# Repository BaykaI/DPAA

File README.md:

# DPAA — ЦАФАР, которую можно услышать

Проект демонстрации принципов **цифровой активной фазированной антенной решётки
(ЦАФАР)** в акустическом диапазоне: вместо антенн — динамики и микрофоны, вместо
СВЧ — звук 1.5–4 кГц, вместо осциллографа — уши зрителей.

Звук в ~875 000 раз медленнее радиоволн, поэтому решётка из восьми динамиков
с шагом 4 см геометрически эквивалентна решётке S-диапазона, а обычная
многоканальная звуковая карта оцифровывает сигнал прямо на «несущей» — то, о чём
мечтают разработчики настоящих ЦАФАР.

Подробная концепция, расчёты, сценарии и варианты железа: **[docs/concept.md](docs/concept.md)**.

**Железо** (16 элементов, ПЛИС ECP5 на модуле Colorlight i9, ≈ 630 $, с резервом ≈ 725 $ из 1000 $):
[архитектура](docs/hardware/architecture.md) · [что купить и заказать](docs/hardware/purchase.md) · [спецификация и бюджет](docs/hardware/bom.md) ·
[схемы плат](docs/hardware/schematics.md) · [распиновка](docs/hardware/pinout.md) ·
[схема соединений](docs/hardware/wiring.md) · [полная структурная схема](docs/img/full_diagram.svg) · [элемент: динамик + микрофон, 3D-модель](docs/hardware/mechanics.md) ·
[прошивка ПЛИС](gateware/README.md)

## Что уже есть

* `dpaa/` — небольшая библиотека моделирования:
  * `geometry.py` — решётки (линейные, плоские), направления, задержки фазирования;
  * `signals.py` — дробные задержки (БПФ и КИХ для реального времени), фазовращатель,
    тестовые сигналы;
  * `patterns.py` — диаграммы направленности, весовые окна, «косоглазие» луча, квантование;
  * `propagation.py` — распространение звука в свободном поле;
  * `transmit.py` — формирование лучей на передачу, многолучевость, сканирование, запись WAV;
  * `beamforming.py` — приём: задержка-сумма, MVDR (Кейпон), «акустическая камера».
* `scripts/`:
  * `design_calc.py` — таблицы параметров решётки;
  * `plot_patterns.py` — иллюстрации в `docs/img/`;
  * `make_tx_demo.py` — 8-канальные WAV для реальной решётки динамиков и
    **моно-WAV «виртуальных слушателей»** — можно послушать эффект в наушниках уже сейчас;
  * `demo_rx_sim.py` — приём двумя лучами и адаптивное подавление помехи.
* `dpaa/hw.py` — аппаратная модель: карта регистров, протокол UART, фиксированная точка,
  эталонная модель ядра ПЛИС (RTL сверяется с ней бит в бит).
* `gateware/` — прошивка ПЛИС на Verilog: I2S на 16 усилителей и 17 микрофонов,
  генераторы, цифровое диаграммообразование на передачу (2 луча) и приём (2 луча).
* `tools/dpaa_ctl.py` — управление с ноутбука: луч, сканирование, два луча, фокус,
  поэлементный тест, лучи приёма в наушники, уровни микрофонов.
* `software/DpaaControl/` — **пульт управления на C#** (.NET 8 + Avalonia, Windows/Linux/macOS):
  все сценарии `dpaa_ctl.py` с ползунками, план зала с лепестком звука, диаграмма
  направленности, уровни микрофонов, симулятор ПЛИС для работы без железа —
  [README](software/DpaaControl/README.md).
* `firmware/esp32/` — **прошивка Wi-Fi-пульта ESP32-S3**: своя сеть Wi-Fi, страница для планшета
  (луч «пальцем», маятник, два луча, прожектор, приём), автопилот для музея, служебная панель —
  [README](firmware/esp32/README.md).
* `tests/` — проверки физики и алгоритмов и RTL-тесты ПЛИС (`pytest`, нужен Icarus Verilog).

## Быстрый старт

```bash
pip install -r requirements.txt
python -m pytest -q                 # тесты
python scripts/design_calc.py       # расчёт параметров
python scripts/plot_patterns.py     # графики -> docs/img/
python scripts/make_tx_demo.py      # WAV -> out/tx/
python scripts/demo_rx_sim.py       # WAV -> out/rx/
```

Послушать без железа: `out/tx/listen_two_beams_-35deg.wav` и `..._+35deg.wav` —
что слышат два человека, стоящие по разные стороны от решётки, воспроизводящей
два луча одновременно; `out/tx/listen_prism_phase_*` — «звуковая призма»;
`out/rx/mic1.wav` vs `out/rx/mvdr_target.wav` — подавление помехи на приёме.

## Соглашения

Решётка лежит вдоль оси x и излучает вдоль +y. Угол отсчитывается от нормали,
положительные углы — вправо, если стоять за решёткой и смотреть в направлении
излучения. Канал 1 многоканального WAV — крайний левый элемент.

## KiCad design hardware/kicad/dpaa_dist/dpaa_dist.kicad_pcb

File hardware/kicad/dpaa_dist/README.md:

# Распределительная плата DPAA (A3) — проект KiCad 10

Плата 100 × 180 мм, два слоя, все компоненты на верхней стороне, сборка на фабрике (JLCPCB/PCBWay).
13 буферов 74LVC244 (SOIC-20W; U1–U8 — такты пары соседних элементов, U9–U12 — TXD/MIC четырёх
элементов, U13 — ЦАП и зонд), ЦАП PCM5102A, драйвер наушников TDA1308, два стабилизатора
AP2112K-3.3, защита питания (P-MOSFET AO4407A, TVS SMBJ5.0A, 1000 мкФ), 4 предохранителя PTC,
16 гребёнок элементов 2×6, три вилки IDC 2×15 к плате ПЛИС (P1 — Ethernet, P2, P3 — сигналы), RJ45 зонда,
гнездо Ethernet RJ45 с трансформаторами (MagJack), ESP32, наушники.
Схема — [`../../../docs/hardware/schematics.md`](../../../docs/hardware/schematics.md).

## Файлы

| Файл | Что |
|---|---|
| `dpaa_dist.kicad_pro`, `.kicad_sch`, `.kicad_pcb` | проект, схема, плата (открываются в KiCad 10) |
| `fab/dpaa_dist_gerber.zip` | Gerber (RS-274X) + Excellon + карта сверловки |
| `fab/dpaa_dist_bom_jlcpcb.csv`, `fab/dpaa_dist_cpl_jlcpcb.csv` | BOM и координаты SMD в формате JLCPCB |
| `fab/dpaa_dist_bom.csv`, `fab/dpaa_dist_pos.csv` | BOM (с наименованиями для заказа) и координаты всех компонентов |
| `fab/dpaa_dist_top.pdf`, `_bottom.pdf`, `_assembly.pdf`, `_schematic.pdf` | слои, сборочный чертёж, схема |
| `fab/render_top.png`, `render_bottom.png`, `render_3d.png`, `dpaa_dist.step` | 3D-вид и модель |
| `drc.json`, `erc.json` | отчёты DRC/ERC (сводка — `python gen/drc_report.py`) |

## Как собрано

Схема и плата **генерируются скриптами** (`gen/`), вручную в KiCad ничего не рисовалось:

* `gen/place.py` — компоновка и цепи (все корпуса — в узлах сетки 0,635 мм);
* `gen/router.py` — трассировщик по сетке (A*, два слоя: верхний — горизонтали, нижний — вертикали,
  перекладка мешающих цепей при неудаче);
* `gen/make_board.py` — сборка платы: силовые шины 1 мм вручную (+5 В по нижнему краю, 5 В групп
  и 3V3_MIC вдоль боковых краёв), остальные цепи — трассировщиком (0,25 мм, переходные 0,6/0,3),
  земля — дорожками и полигонами на обоих слоях, затем проход `miter_corners()`: каждый прямой
  угол заменяется двумя поворотами по 45° (прямых углов на дорожках нет);
* `gen/make_sch.py` — схема из платы: прямоугольные символы с номерами выводов посадочных мест,
  цепи — глобальными метками (ERC сверяет схему с платой по именам цепей);
* `gen/fix_pro.py` — нормы фабрики в проекте: зазор 0,2, дорожка 0,2, отверстие 0,3, медь до края 0,3.

Запуск: `gen/build.sh` (плата → DRC → схема → ERC → сводка), затем `gen/export.sh` (пакет для фабрики).
Нужны KiCad 10 (`kicad-cli`, его Python) и системный Python 3.

## Нумерация и назначение разъёмов

* **J1–J16** — элементы 1–16 (J1–J8 слева сверху вниз, J9–J16 справа), контакт 1 у края платы:
  нечётный ряд — к модулю усилителя MAX98357A, чётный — к микрофону ICS-43434 (таблица в
  [`pinout.md`](../../../docs/hardware/pinout.md)). 5 В на контакт 1 идёт через предохранитель
  своей группы: F1 — J1–J4, F2 — J5–J8, F3 — J9–J12, F4 — J13–J16.
* **J19** = гребёнка **P1** (Ethernet), **J20** = гребёнка **P2**, **J21** = гребёнка **P3** платы расширения
  Colorlight i9: три одинаковых прямых шлейфа IDC 2×15 (жила n → контакт n обоих разъёмов). Гребёнки платы
  расширения нумерованы «1–15 в одном ряду, 16–30 в другом (30 напротив 1)», а вилка IDC — зигзагом
  (1, 2 в первой колонке, 3, 4 во второй…); прямой шлейф соединяет контакты **по положению**, поэтому
  на плате сигнал контакта *d* гребёнки стоит на контакте вилки 2d−1 (d ≤ 15) или 2·(31−d) (d ≥ 16) —
  это учтено в генераторе (`dip2k()` в `gen/place.py`). Ключ вилки — в сторону контакта 1; на плате
  расширения ключа нет, контакт 1 шлейфа (цветная жила) — на контакт 1 гребёнки (у надписи P1/P2/P3).
  Контакты 3V3 и 5V гребёнок на плате не подключены.
* **J17** — RJ45 зонда (T568B: 1 BCLK, 3 LRCLK, 4–5 3V3_MIC, 7 SD, 2/6/8 GND).
* **J18** — питание 5 В 5.5/2.1 мм (центр «+»); **J25** — ESP32 (TX, RX, GND); **J26, J27** — наушники.
* **SW1** — кнопка «тестовый тон» (BTN_TEST → 3,3 В); LED1 — 5 В, LED2 — 3,3 В логики.

## Ethernet (J19 → J29)

Что это. На модуле Colorlight i9 стоят два гигабитных PHY Broadcom B50612D; их линейные пары MDI
(после PHY, без трансформаторов) выведены на гребёнку **P1** платы расширения. На распределительной
плате порт ETH1 заведён на гнездо **J29** — RJ45 MagJack **UDE RB1-125B8G1A** (LCSC C363353,
1000BASE-T, трансформаторы, терминация Боба Смита 75 Ом × 4 + 1000 пФ 2 кВ внутри — её общий вывод R10
и экран SH сидят на отдельной цепи **CHASSIS**). Цепь CHASSIS — отдельный полигон под гнездом на обоих
слоях (земля под гнездом вырезана), с сигнальной землёй связана через C306 1 нФ 2 кВ ‖ R306 1 МОм.
Центральный отвод стороны PHY (R1) — C301 100 нФ на землю; R301 0 Ом (не ставится) подключит его к
3,3 В, если PHY окажется с токовым выходным каскадом (по схеме оригинальной платы Colorlight). ETH2 на
плату не выведен (места у края нет). Светодиоды гнезда не подключены.

Прошивка ПЛИС с MAC (RGMII, LiteX/LiteEth) делается отдельно; эта плата — только физика.

Шлейф W3 (P1 → J19): такой же IDC 2×15, **не длиннее 15–20 см**. Пары на шлейфе: 2P/2N — жилы 1 и 3,
4P/4N — 2 и 4, 1N/1P — 5 и 7, 3N/3P — 6 и 8 (они чередуются, не соседние — так разведена гребёнка P1).
Гигабит по такому шлейфу не гарантирован, 100 Мбит — надёжно; альтернатива — обжать кусок CAT5 на
гнездо 2×15 (пара в пару).

Полярность: у гребёнки P1 в парах 1 и 3 сначала идёт N, в парах 2 и 4 — P, а у гнезда порядок
один (+, −). Чтобы пары не пересекались на плате, пары 2 и 4 подключены к гнезду с обратной
полярностью (2P → TD2−, 2N → TD2+, 4P → TD4−, 4N → TD4+); PHY исправляет полярность автоматически
(10BASE-T по link-pulse, 100/1000 — по коду). Если линк не поднимется — проверить это первым.

Расчёт пар. Двухслойная плата FR4 1,5 мм, медь 35 мкм: одиночная дорожка 0,25 мм над землёй
на обратной стороне имеет Z₀ ≈ 130 Ом (микрополосок, h = 1,5 мм, εr ≈ 4,5); пара 0,25/0,2 даёт
Zдифф ≈ 2·Z₀·(1 − 0,48·e^(−0,96·s/h)) ≈ 150 Ом, а для 100 Ом понадобилась бы пара ≈ 1,2/0,2 мм —
на шаге выводов гнезда 1,27 мм и гребёнки 2,54 мм такое не уложить. Поэтому пары разведены
0,25/≈1,0 (шейки 0,2 мм между площадками внутреннего ряда гнезда), длина каждой линии 11–17 мм —
это ≤ λ/60 даже на 125 МГц (λ ≈ 1,2 м в FR4), рассогласование на такой длине не сказывается.
Пары 1, 2 — верхний слой, пары 3, 4 — нижний (разные ряды гребёнки, иначе пересечения), под парами
сплошная земля другого слоя, другие цепи не ближе 1 мм, переходных на парах нет. Длины линий —
`gen/eth_lengths.txt`; разница внутри пары до 3 мм (≈ 20 пс): обусловлена двумя рядами площадок гнезда
(внешний ряд достижим только шейкой через внутренний), меандр на таком месте не умещается.

## Нормы заказа

Два слоя, FR4 1,5 мм, медь 35 мкм, финиш HASL (или ENIG), маска зелёная, шелкография белая, 100 × 180 мм.
Минимальные нормы в проекте: дорожка 0,2 / зазор 0,2 (использовано 0,25/0,2; шины питания 0,5 и 1,0),
переходные 0,6/0,3 (меньше «лодочных» 0,7/0,35 — на шаге сетки трассировщика 0,635 мм переходное 0,7
не проходит зазор 0,2 к соседней дорожке; у JLCPCB/PCBWay и Резонита 0,3 мм — допустимое сверло),
медь до края 0,3, отверстие до меди 0,25. Журнал скоса углов — `gen/miter_log.txt`
(прямых стыков двух дорожек после прохода не остаётся).

Отличие от «лодочных» плат: нижний слой — не сплошная земля, а второй сигнальный слой
(вертикальные дорожки) с заливкой земли в остатках; земля дополнительно проложена дорожками
и сшита переходными. При 267 цепях и 206 компонентах на 100 × 160 мм сплошной земли внизу
не получается.

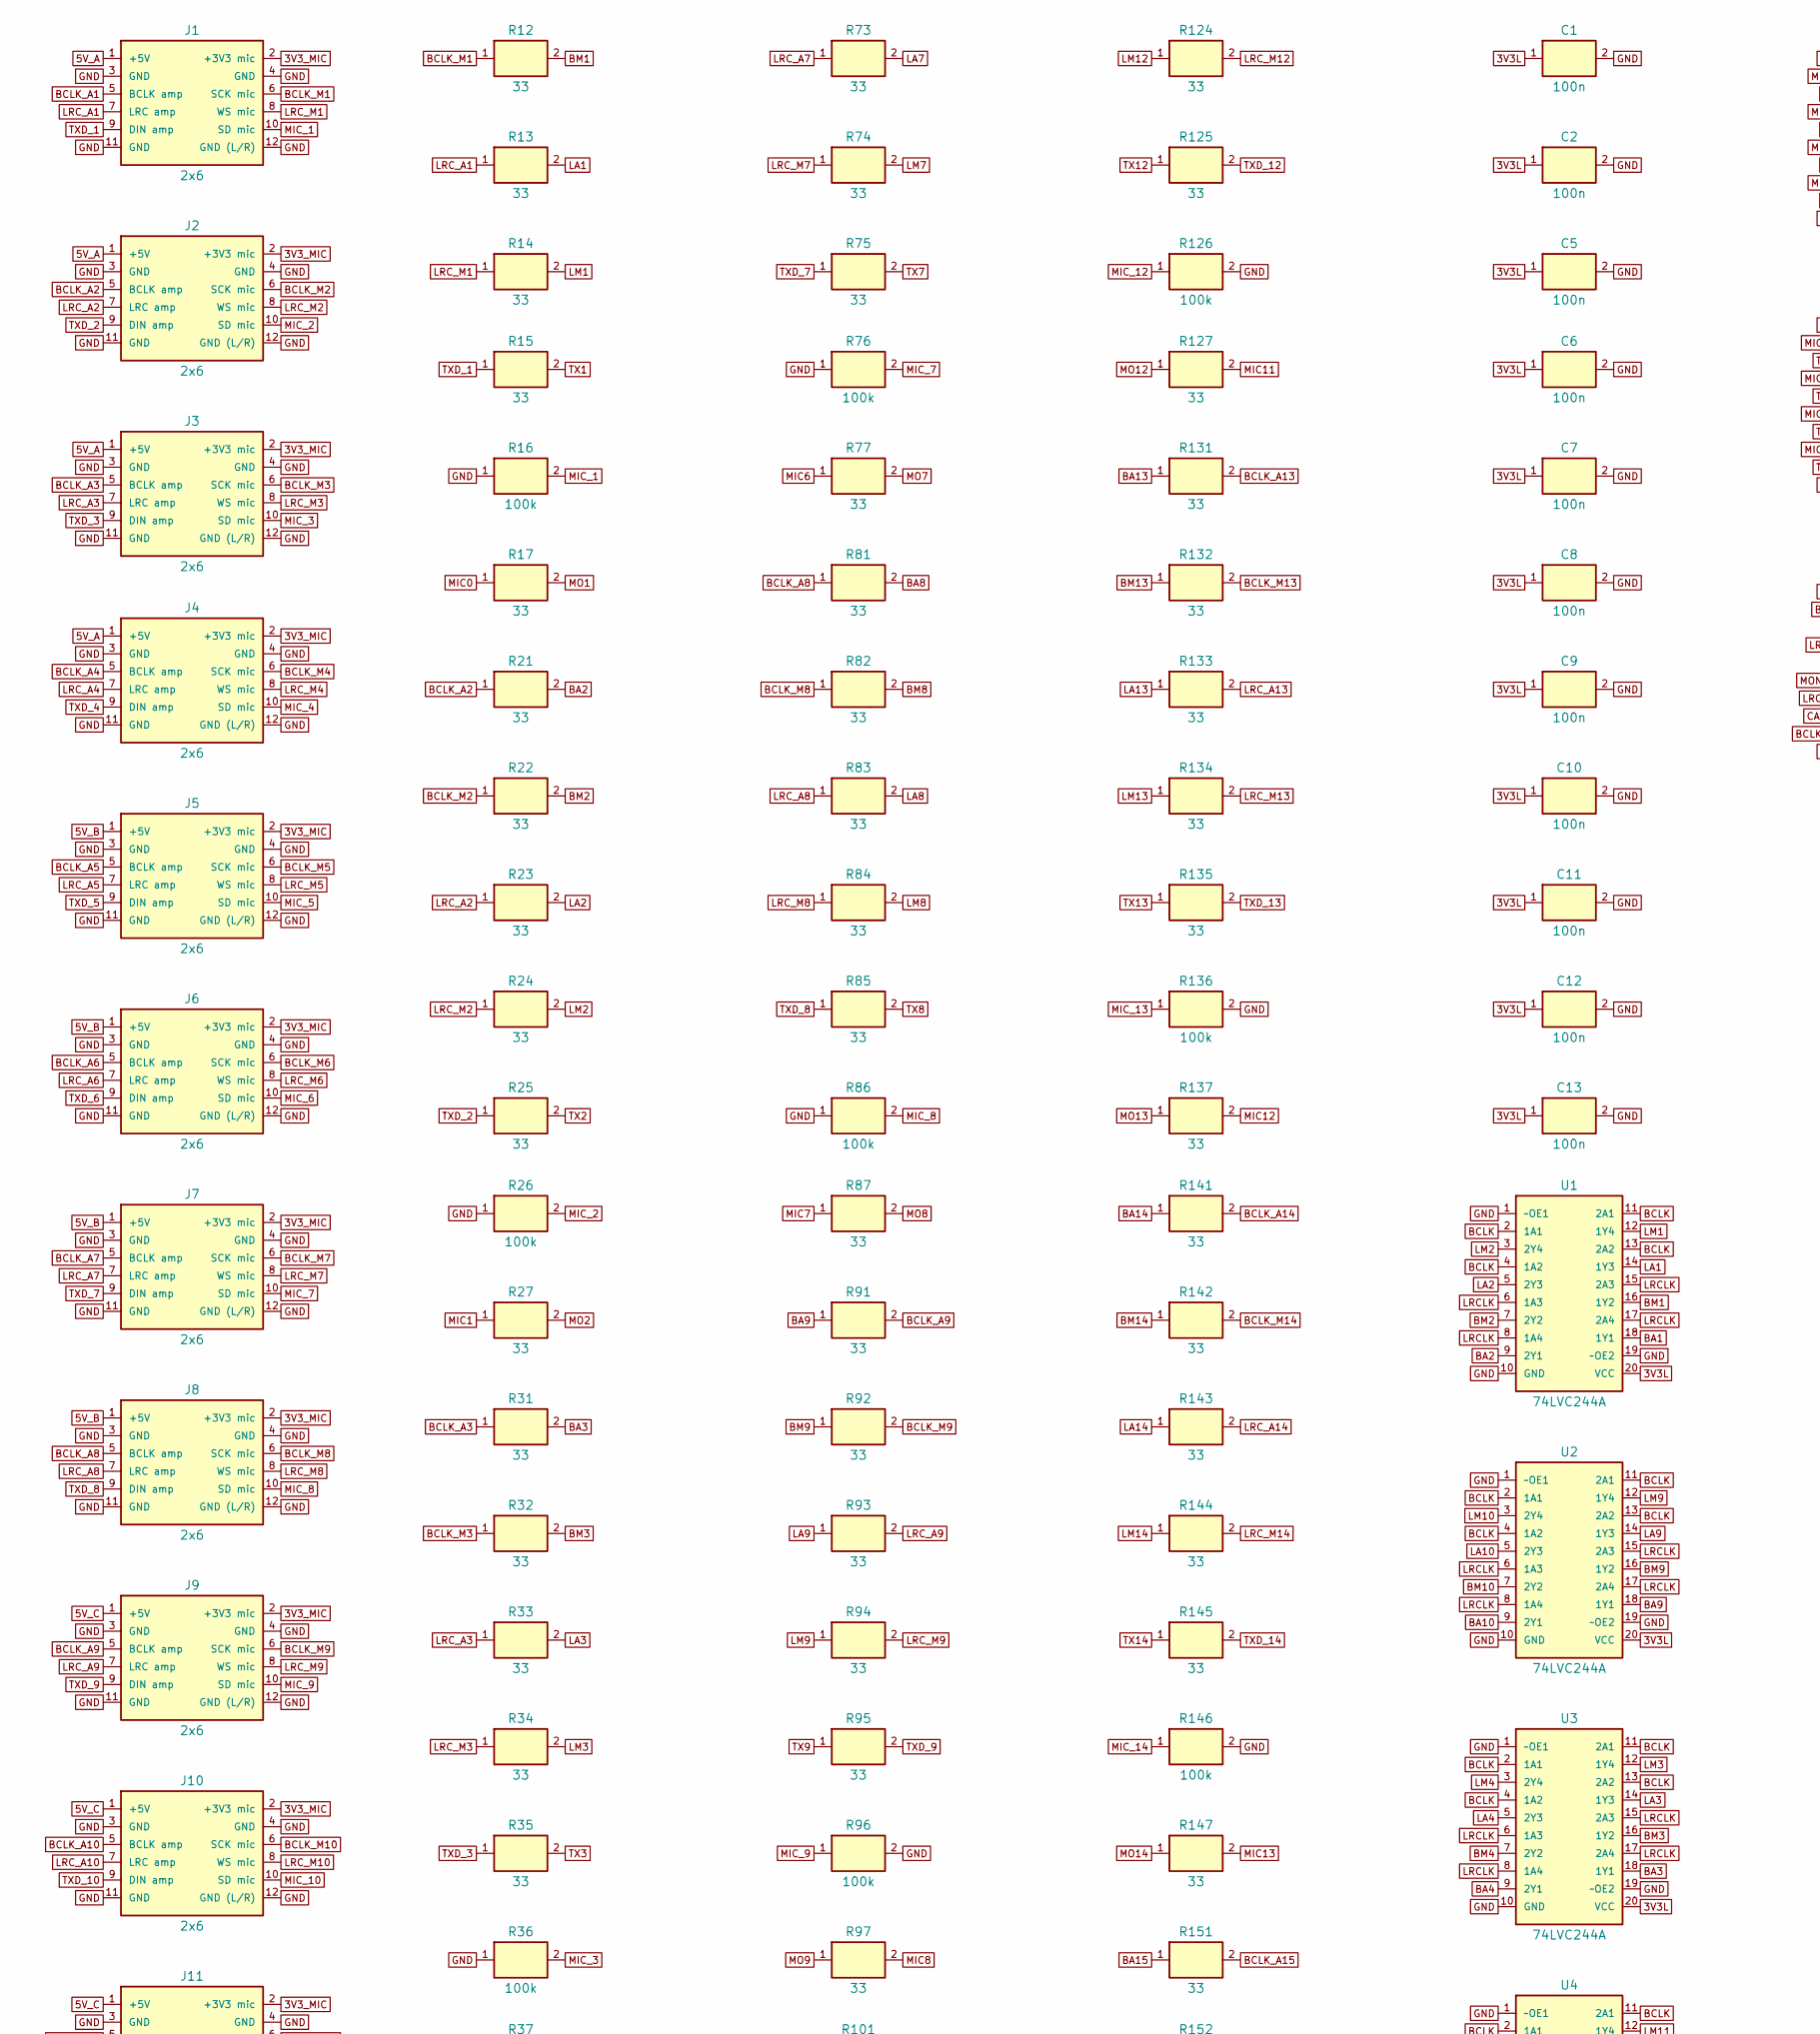
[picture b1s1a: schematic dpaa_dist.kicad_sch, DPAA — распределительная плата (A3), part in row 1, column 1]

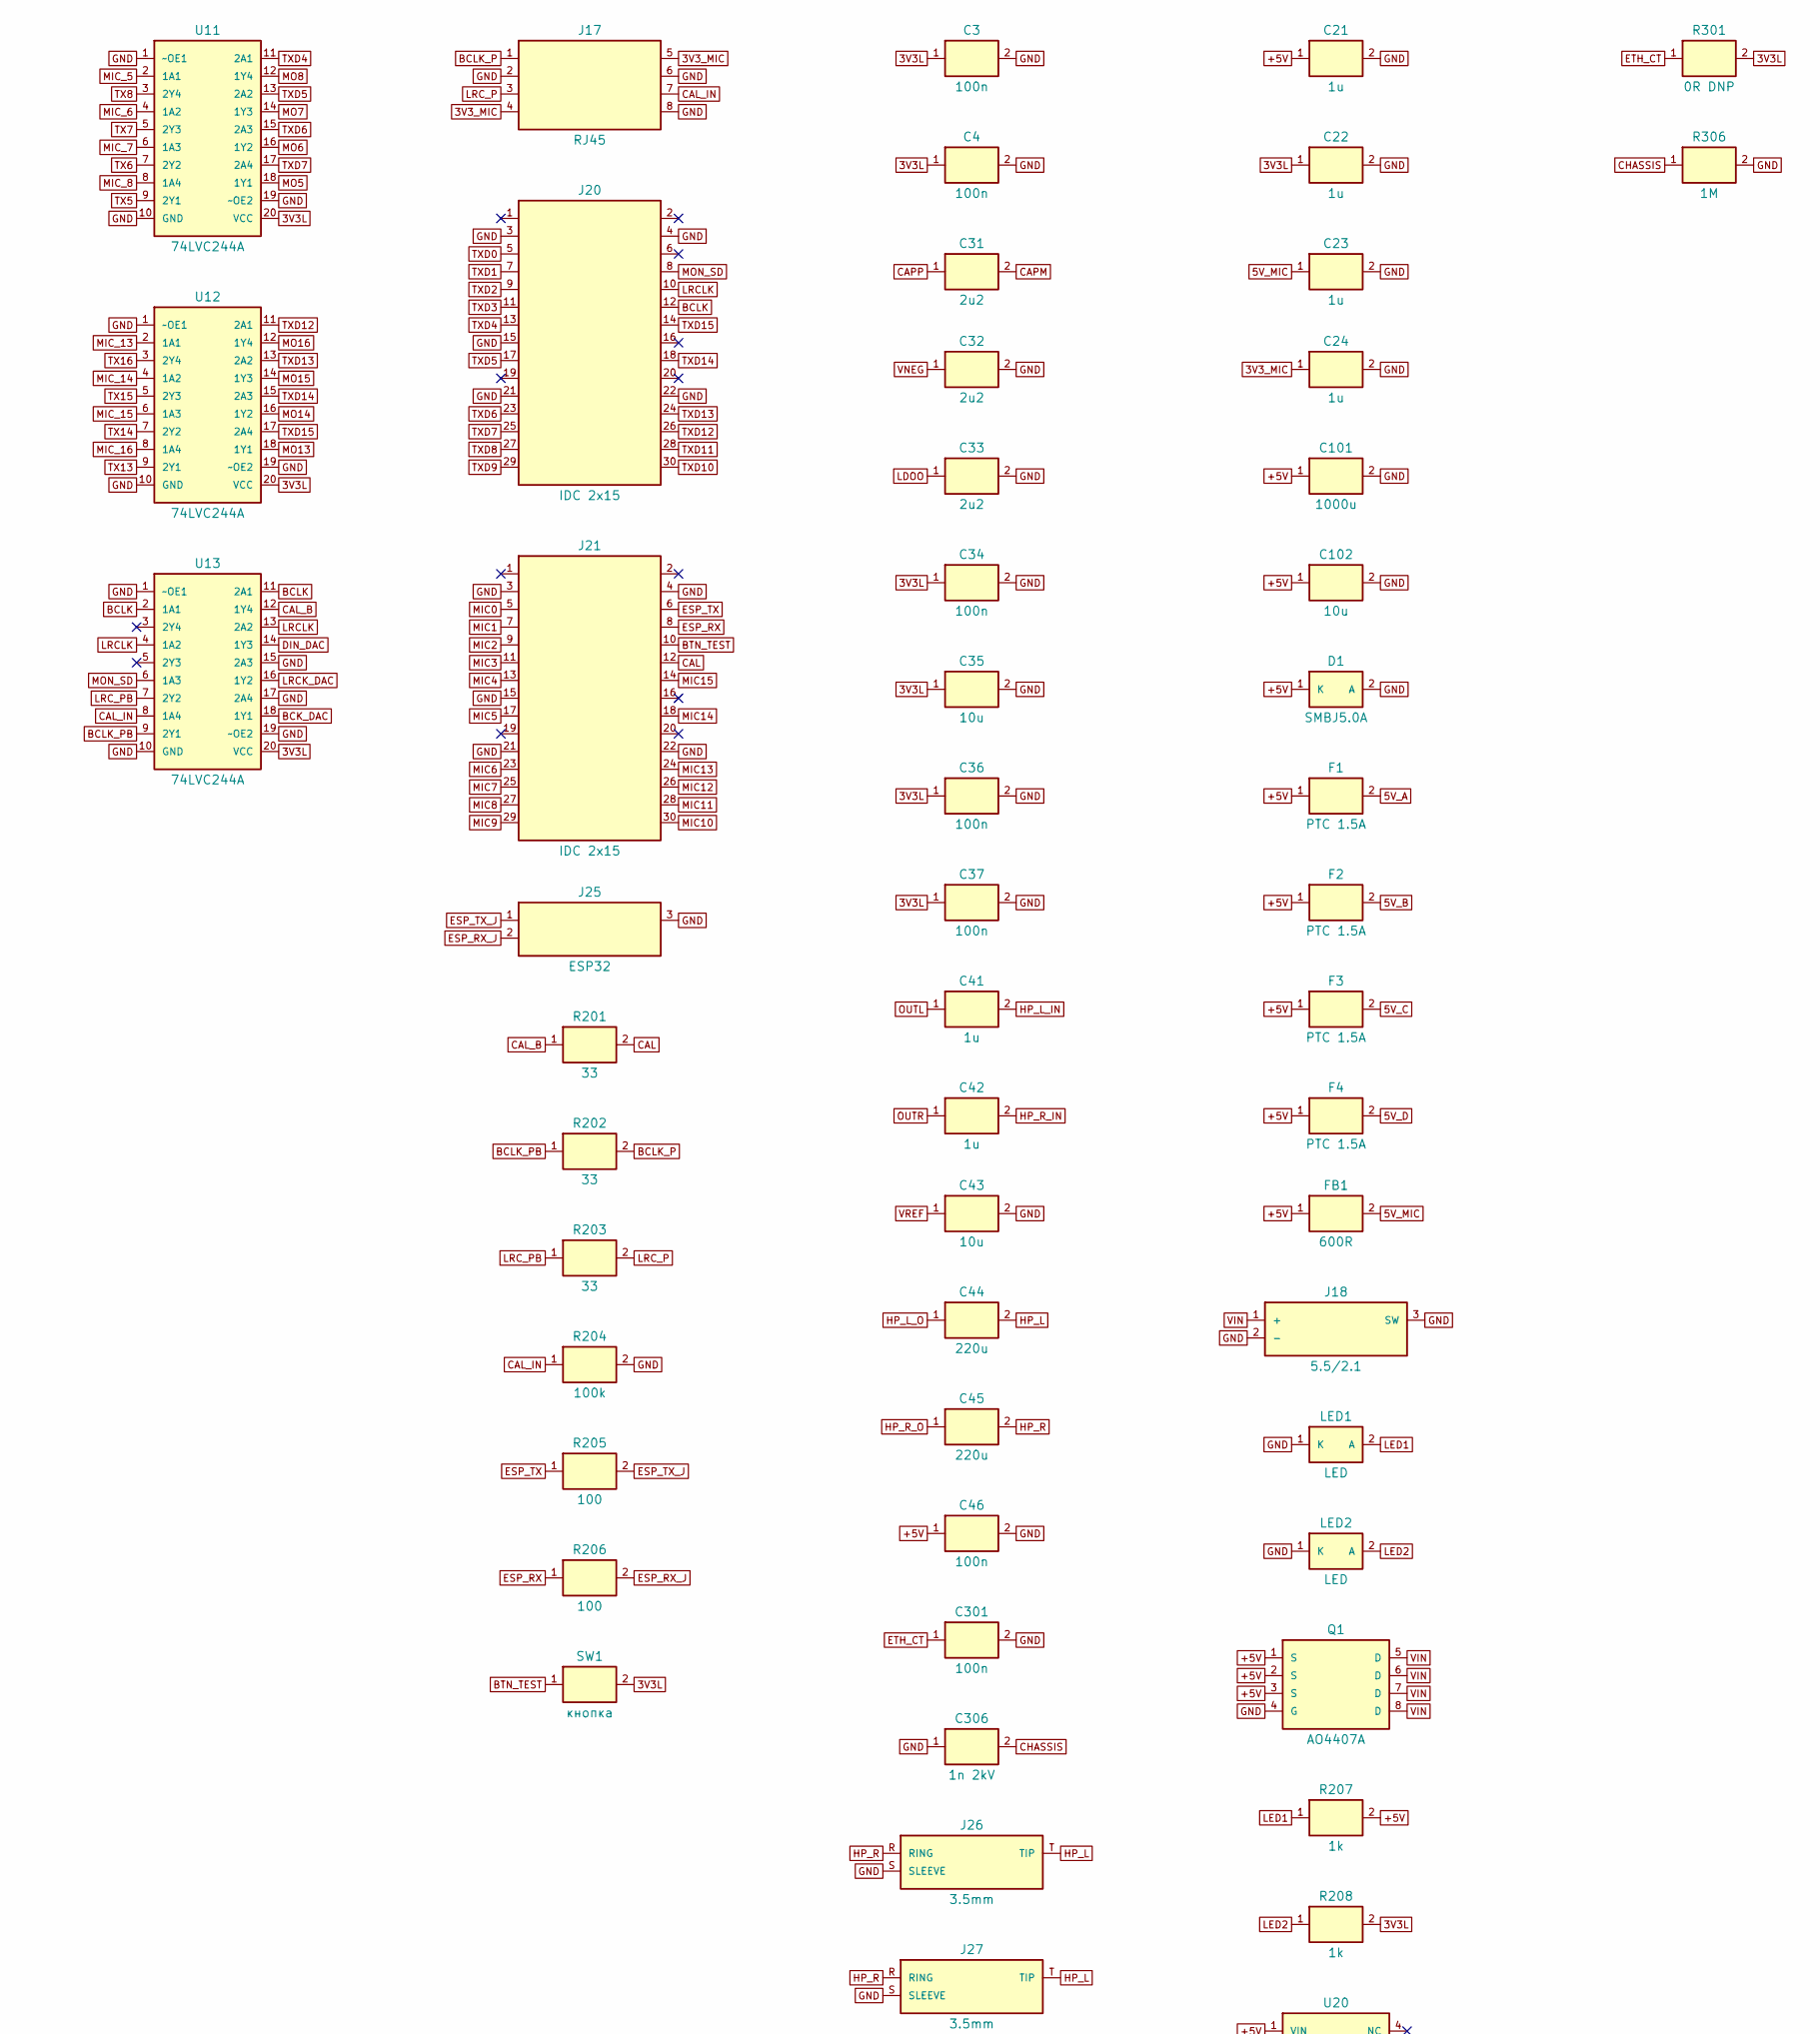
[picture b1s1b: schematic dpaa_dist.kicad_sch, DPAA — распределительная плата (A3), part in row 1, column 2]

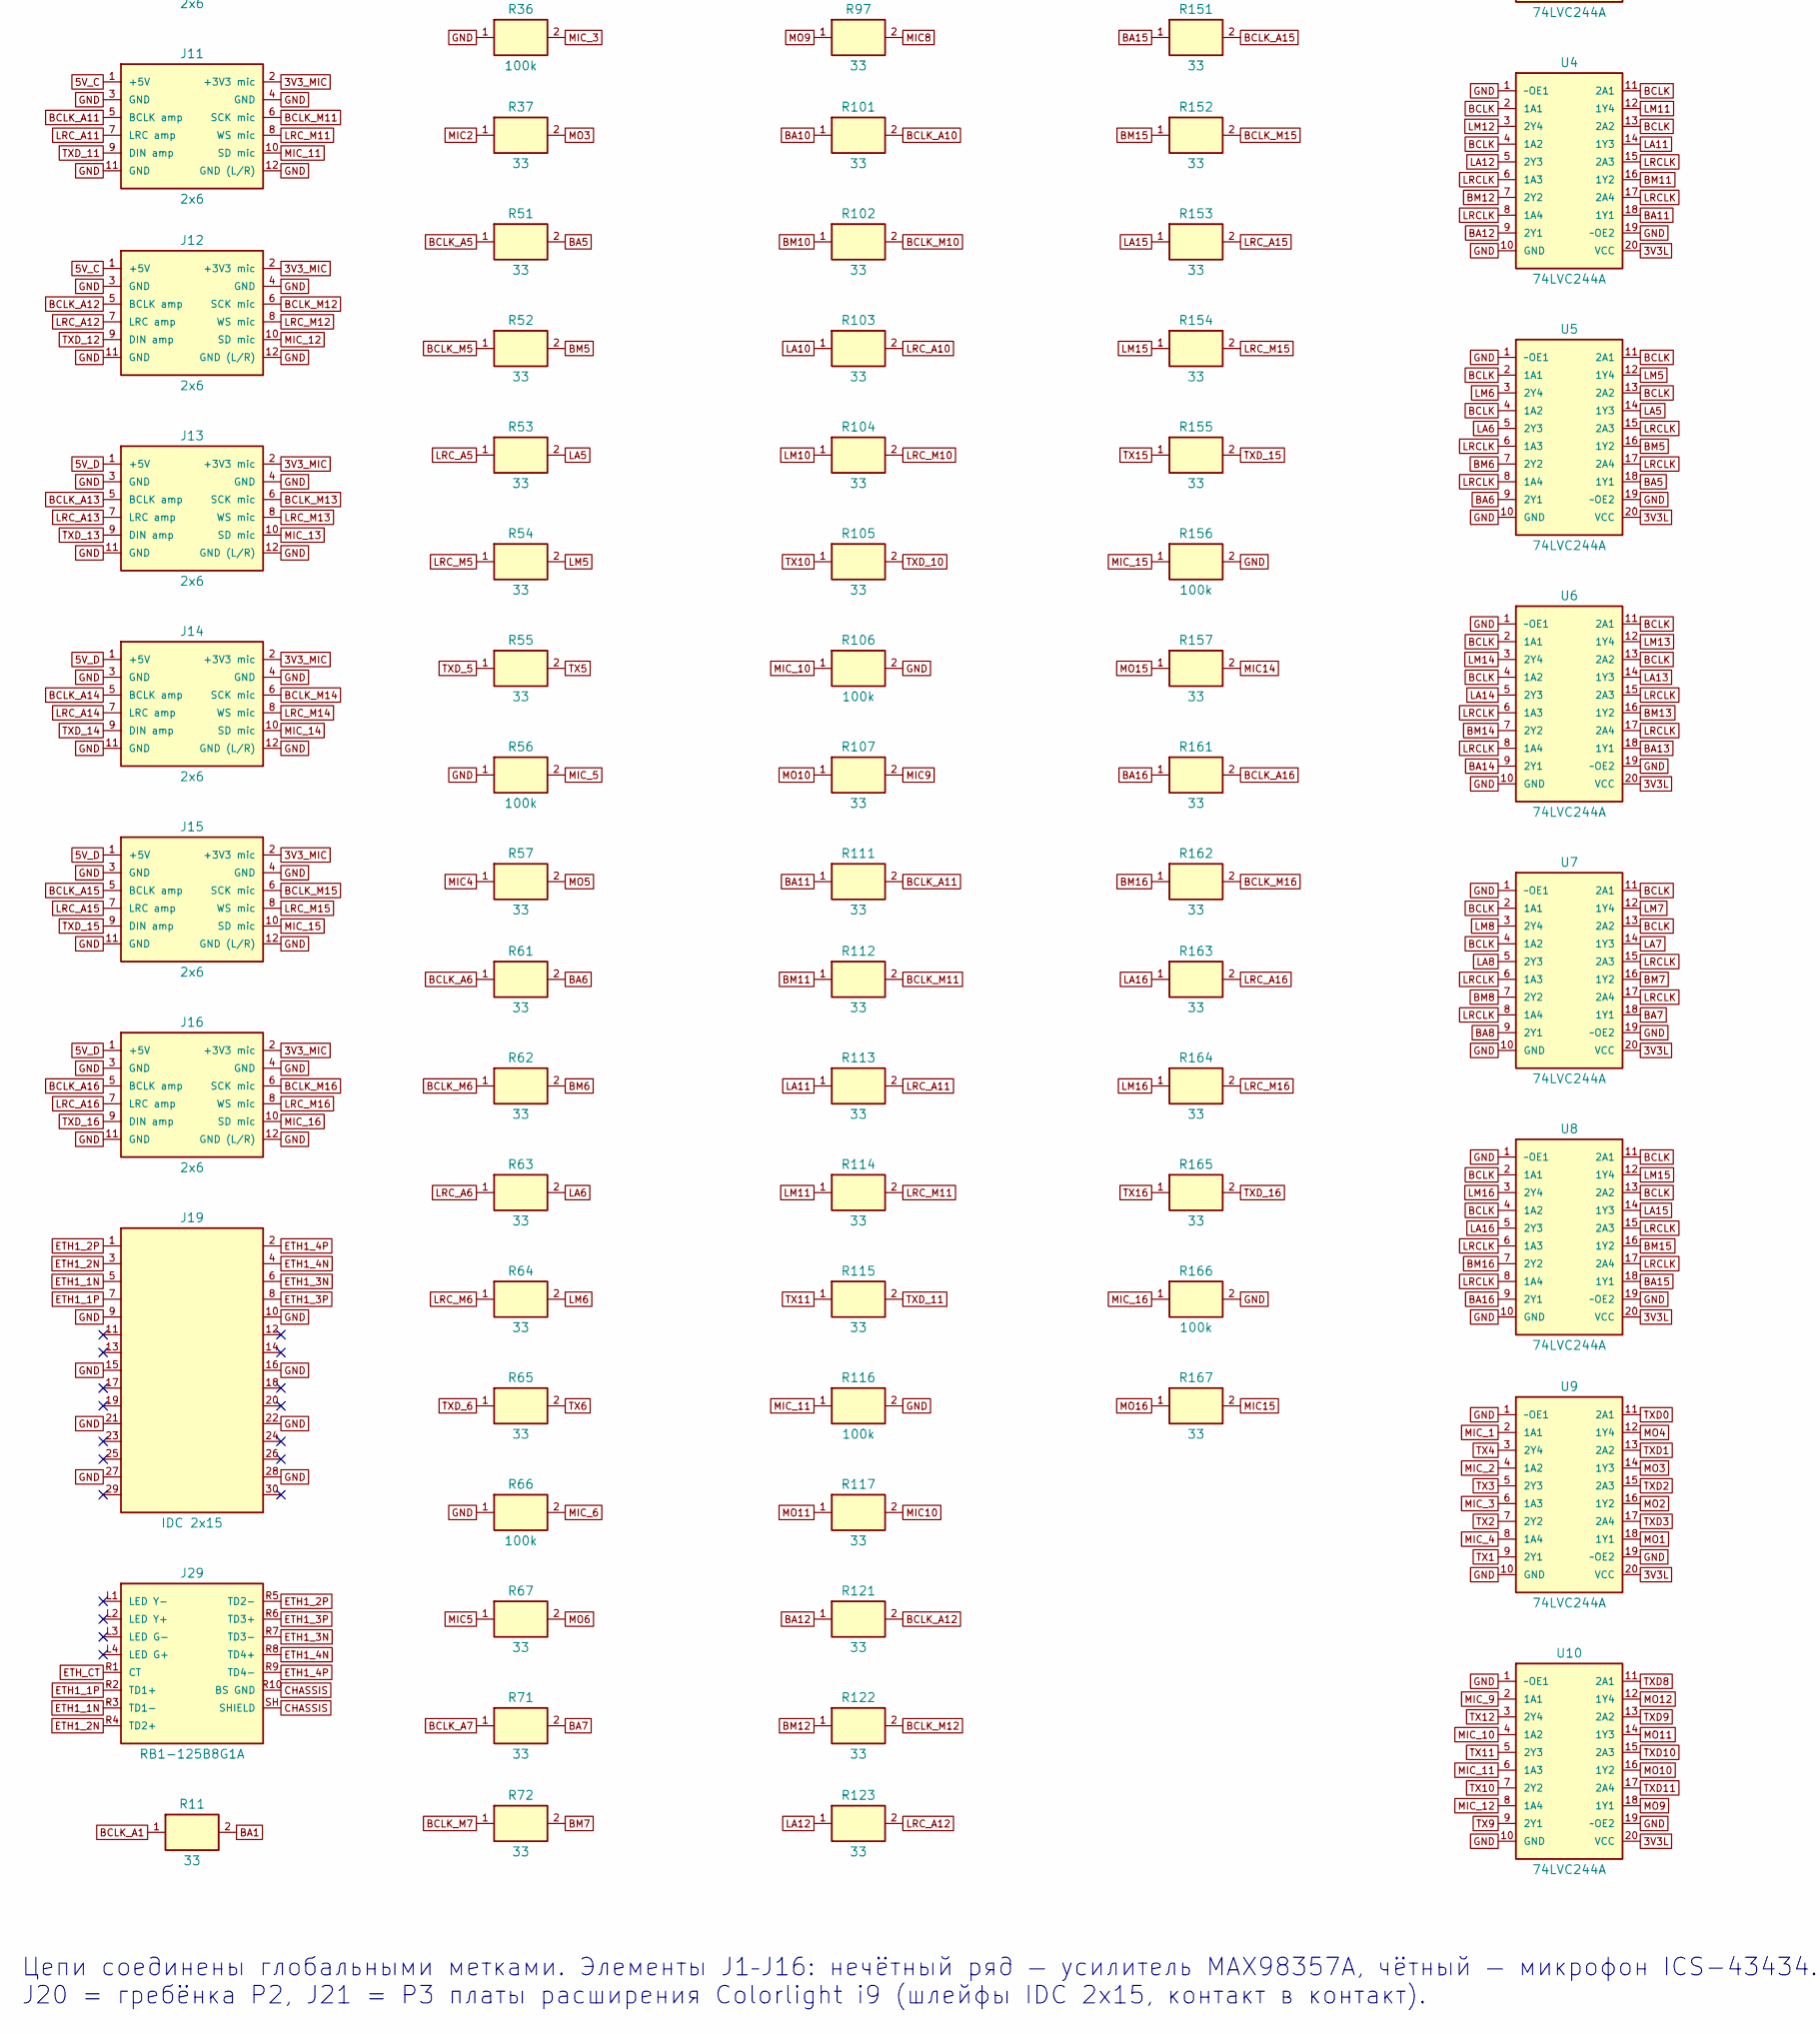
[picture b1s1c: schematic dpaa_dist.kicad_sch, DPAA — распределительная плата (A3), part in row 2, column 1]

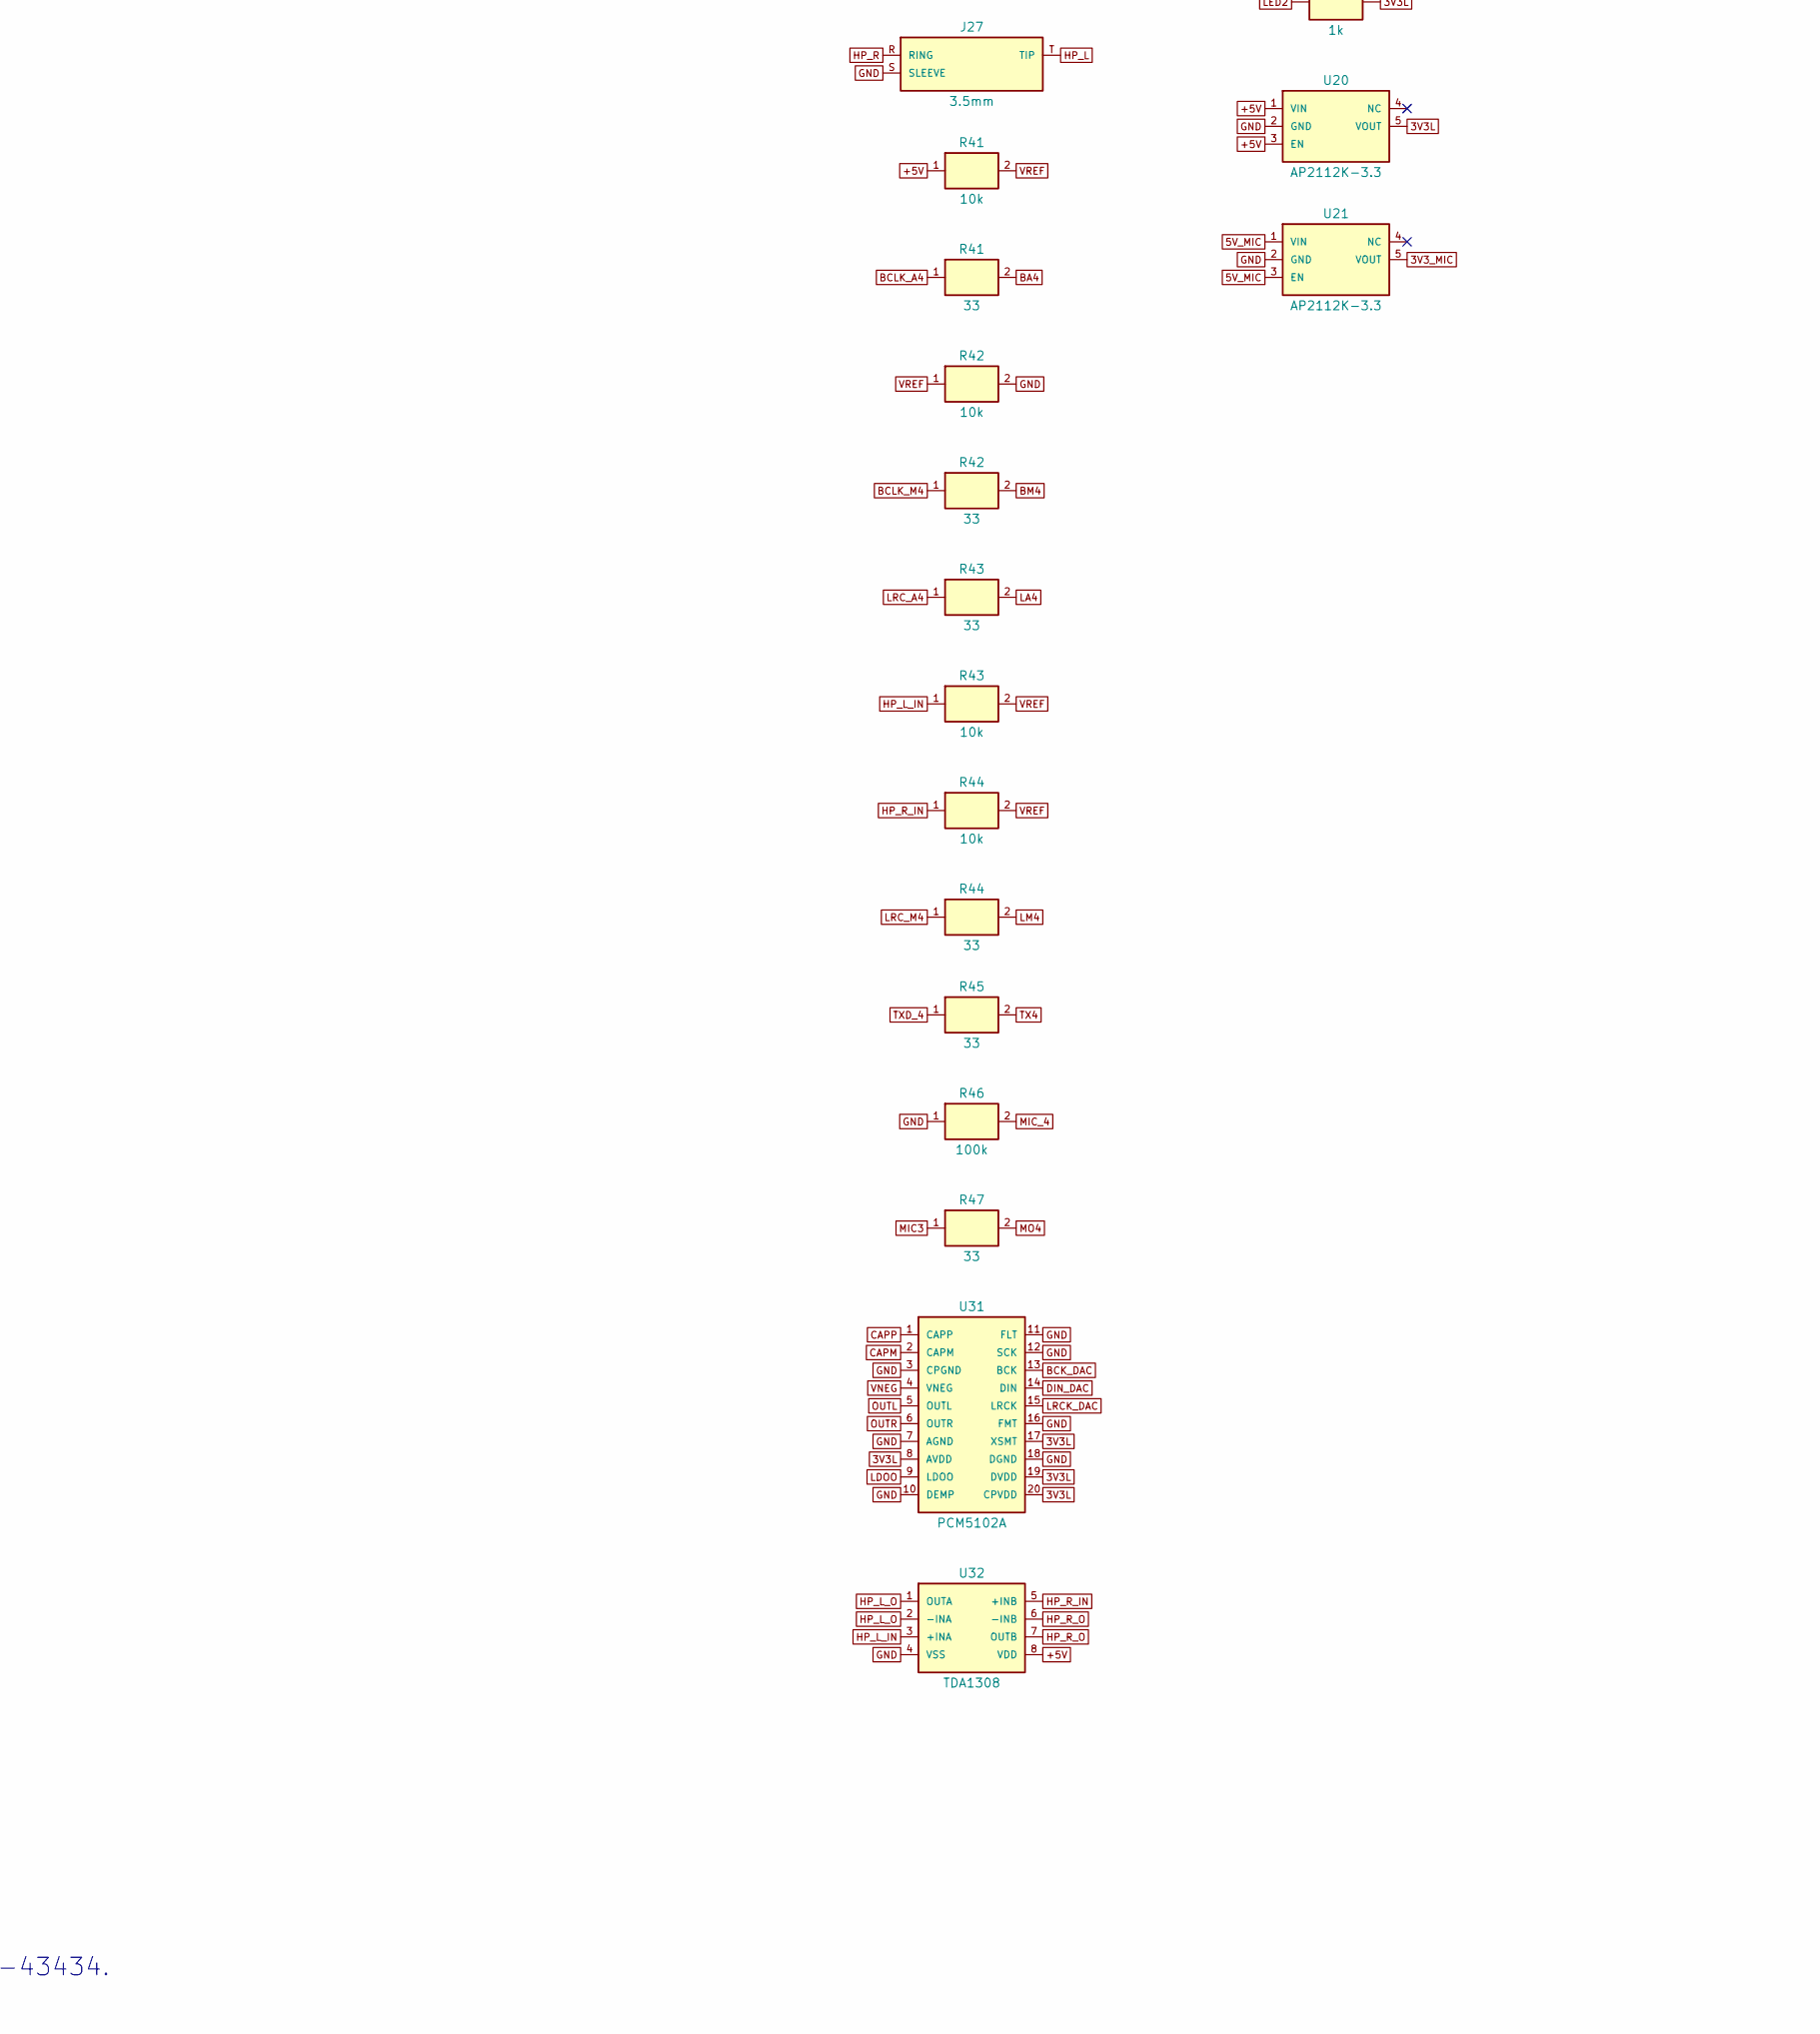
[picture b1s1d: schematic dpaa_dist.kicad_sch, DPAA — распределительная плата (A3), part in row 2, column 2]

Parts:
C1, C2, C3, C4, C5, C6, C7, C8, C9, C10, C11, C12, C13, C34, C36, C37, C46, C301: 100n; C_0603_1608Metric
C21, C22, C23, C24, C41, C42: 1u; C_0805_2012Metric
C31, C32, C33: 2u2; C_0805_2012Metric
C35, C43, C102: 10u; C_0805_2012Metric
C44, C45: 220u; CP_Radial_D6.3mm_P2.50mm
C101: 1000u; CP_Radial_D10.0mm_P5.00mm
C306: 1n 2kV; C_1812_4532Metric
D1: SMBJ5.0A; D_SMB
F1, F2, F3, F4: PTC 1.5A; Fuse_1812_4532Metric
FB1: 600R; L_0805_2012Metric
J1, J2, J3, J4, J5, J6, J7, J8, J9, J10, J11, J12, J13, J14, J15, J16: 2x6; PinHeader_2x06_P2.54mm_Vertical
J17: RJ45; RJ45_Amphenol_54602-x08_Horizontal
J18: 5.5/2.1; BarrelJack_Horizontal
J19, J20, J21: IDC 2x15; IDC-Header_2x15_P2.54mm_Vertical
J25: ESP32; PinHeader_1x03_P2.54mm_Vertical
J26, J27: 3.5mm; Jack_3.5mm_CUI_SJ1-3523N_Horizontal
J29: RB1-125B8G1A; RJ45_UDE_RB1-125B8G1A
LED1, LED2: LED; LED_0603_1608Metric
Q1: AO4407A; SOIC-8_3.9x4.9mm_P1.27mm
R11, R12, R13, R14, R15, R17, R21, R22, R23, R24, R25, R27, R31, R32, R33, R34, R35, R37, R43, R45, R47, R51, R52, R53, R54, R55, R57, R61, R62, R63, R64, R65, R67, R71, R72, R73, R74, R75, R77, R81, R82, R83, R84, R85, R87, R91, R92, R93, R94, R95, R97, R101, R102, R103, R104, R105, R107, R111, R112, R113, R114, R115, R117, R121, R122, R123, R124, R125, R127, R131, R132, R133, R134, R135, R137, R141, R142, R143, R144, R145, R147, R151, R152, R153, R154, R155, R157, R161, R162, R163, R164, R165, R167, R201, R202, R203: 33; R_0603_1608Metric
R16, R26, R36, R46, R56, R66, R76, R86, R96, R106, R116, R126, R136, R146, R156, R166, R204: 100k; R_0603_1608Metric
R41, R42, R44: 10k; R_0603_1608Metric
R205, R206: 100; R_0603_1608Metric
R207, R208: 1k; R_0603_1608Metric
R301: 0R DNP; R_0603_1608Metric
R306: 1M; R_0603_1608Metric
SW1: кнопка; SW_Push_1TS009xxxx-xxxx-xxxx_6x6x5mm
U1, U2, U3, U4, U5, U6, U7, U8, U9, U10, U11, U12, U13: 74LVC244A; SOIC-20W_7.5x12.8mm_P1.27mm
U20, U21: AP2112K-3.3; SOT-23-5
U31: PCM5102A; TSSOP-20_4.4x6.5mm_P0.65mm
U32: TDA1308; SOIC-8_3.9x4.9mm_P1.27mm

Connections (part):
3V3L: C1.1, C2.1, C3.1, C4.1, C5.1, C6.1, C7.1, C8.1, C9.1, C10.1, C11.1, C12.1, C13.1, C22.1, C34.1, C35.1, C36.1, C37.1, R208.2, R301.2, SW1.2, U1.20 (VCC), U2.20 (VCC), U3.20 (VCC), U4.20 (VCC), U5.20 (VCC), U6.20 (VCC), U7.20 (VCC), U8.20 (VCC), U9.20 (VCC), U10.20 (VCC), U11.20 (VCC), U12.20 (VCC), U13.20 (VCC), U20.5 (VOUT), U31.8 (AVDD), U31.17 (XSMT), U31.19 (DVDD), U31.20 (CPVDD)
3V3_MIC: C24.1, J1.2 (+3V3 mic), J2.2 (+3V3 mic), J3.2 (+3V3 mic), J4.2 (+3V3 mic), J5.2 (+3V3 mic), J6.2 (+3V3 mic), J7.2 (+3V3 mic), J8.2 (+3V3 mic), J9.2 (+3V3 mic), J10.2 (+3V3 mic), J11.2 (+3V3 mic), J12.2 (+3V3 mic), J13.2 (+3V3 mic), J14.2 (+3V3 mic), J15.2 (+3V3 mic), J16.2 (+3V3 mic), J17.4, J17.5, U21.5 (VOUT)
5V_A: F1.2, J1.1 (+5V), J2.1 (+5V), J3.1 (+5V), J4.1 (+5V)
5V_B: F2.2, J5.1 (+5V), J6.1 (+5V), J7.1 (+5V), J8.1 (+5V)
5V_C: F3.2, J9.1 (+5V), J10.1 (+5V), J11.1 (+5V), J12.1 (+5V)
5V_D: F4.2, J13.1 (+5V), J14.1 (+5V), J15.1 (+5V), J16.1 (+5V)
5V_MIC: C23.1, FB1.2, U21.1 (VIN), U21.3 (EN)
BA1: R11.2, U1.18 (1Y1)
BA2: R21.2, U1.9 (2Y1)
BA3: R31.2, U3.18 (1Y1)
BA5: R51.2, U5.18 (1Y1)
BA6: R61.2, U5.9 (2Y1)
BA7: R71.2, U7.18 (1Y1)
BA8: R81.2, U7.9 (2Y1)
BA9: R91.1, U2.18 (1Y1)
BA10: R101.1, U2.9 (2Y1)
BA11: R111.1, U4.18 (1Y1)
BA12: R121.1, U4.9 (2Y1)
BA13: R131.1, U6.18 (1Y1)
BA14: R141.1, U6.9 (2Y1)
BA15: R151.1, U8.18 (1Y1)
BA16: R161.1, U8.9 (2Y1)
BCK_DAC: U13.18 (1Y1), U31.13 (BCK)
BCLK: J20.12, U1.2 (1A1), U1.4 (1A2), U1.11 (2A1), U1.13 (2A2), U2.2 (1A1), U2.4 (1A2), U2.11 (2A1), U2.13 (2A2), U3.2 (1A1), U3.4 (1A2), U3.11 (2A1), U3.13 (2A2), U4.2 (1A1), U4.4 (1A2), U4.11 (2A1), U4.13 (2A2), U5.2 (1A1), U5.4 (1A2), U5.11 (2A1), U5.13 (2A2), U6.2 (1A1), U6.4 (1A2), U6.11 (2A1), U6.13 (2A2), U7.2 (1A1), U7.4 (1A2), U7.11 (2A1), U7.13 (2A2), U8.2 (1A1), U8.4 (1A2), U8.11 (2A1), U8.13 (2A2), U13.2 (1A1), U13.11 (2A1)
BCLK_A1: J1.5 (BCLK amp), R11.1
BCLK_A2: J2.5 (BCLK amp), R21.1
BCLK_A3: J3.5 (BCLK amp), R31.1
BCLK_A5: J5.5 (BCLK amp), R51.1
BCLK_A6: J6.5 (BCLK amp), R61.1
BCLK_A7: J7.5 (BCLK amp), R71.1
BCLK_A8: J8.5 (BCLK amp), R81.1
BCLK_A9: J9.5 (BCLK amp), R91.2
BCLK_A10: J10.5 (BCLK amp), R101.2
BCLK_A11: J11.5 (BCLK amp), R111.2
BCLK_A12: J12.5 (BCLK amp), R121.2
BCLK_A13: J13.5 (BCLK amp), R131.2
BCLK_A14: J14.5 (BCLK amp), R141.2
BCLK_A15: J15.5 (BCLK amp), R151.2
BCLK_A16: J16.5 (BCLK amp), R161.2
BCLK_M1: J1.6 (SCK mic), R12.1
BCLK_M2: J2.6 (SCK mic), R22.1
BCLK_M3: J3.6 (SCK mic), R32.1
BCLK_M5: J5.6 (SCK mic), R52.1
BCLK_M6: J6.6 (SCK mic), R62.1
BCLK_M7: J7.6 (SCK mic), R72.1
BCLK_M8: J8.6 (SCK mic), R82.1
BCLK_M9: J9.6 (SCK mic), R92.2
BCLK_M10: J10.6 (SCK mic), R102.2
BCLK_M11: J11.6 (SCK mic), R112.2
BCLK_M12: J12.6 (SCK mic), R122.2
BCLK_M13: J13.6 (SCK mic), R132.2
BCLK_M14: J14.6 (SCK mic), R142.2
BCLK_M15: J15.6 (SCK mic), R152.2
BCLK_M16: J16.6 (SCK mic), R162.2
BCLK_P: J17.1, R202.2
BCLK_PB: R202.1, U13.9 (2Y1)
BM1: R12.2, U1.16 (1Y2)
BM2: R22.2, U1.7 (2Y2)
BM3: R32.2, U3.16 (1Y2)
BM5: R52.2, U5.16 (1Y2)
BM6: R62.2, U5.7 (2Y2)
BM7: R72.2, U7.16 (1Y2)
BM8: R82.2, U7.7 (2Y2)
BM9: R92.1, U2.16 (1Y2)
BM10: R102.1, U2.7 (2Y2)
BM11: R112.1, U4.16 (1Y2)
BM12: R122.1, U4.7 (2Y2)
BM13: R132.1, U6.16 (1Y2)
BM14: R142.1, U6.7 (2Y2)
BM15: R152.1, U8.16 (1Y2)
BM16: R162.1, U8.7 (2Y2)
BTN_TEST: J21.10, SW1.1
CAL: J21.12, R201.2
CAL_B: R201.1, U13.12 (1Y4)
CAL_IN: J17.7, R204.1, U13.8 (1A4)
CAPM: C31.2, U31.2 (CAPM)
CAPP: C31.1, U31.1 (CAPP)
CHASSIS: C306.2, J29.R10 (BS GND), J29.SH (SHIELD), R306.1
DIN_DAC: U13.14 (1Y3), U31.14 (DIN)
ESP_RX: J21.8, R206.1
ESP_RX_J: J25.2, R206.2
ESP_TX: J21.6, R205.1
ESP_TX_J: J25.1, R205.2
ETH1_1N: J19.5, J29.R3 (TD1-)
ETH1_1P: J19.7, J29.R2 (TD1+)
ETH1_2N: J19.3, J29.R4 (TD2+)
ETH1_2P: J19.1, J29.R5 (TD2-)
ETH1_3N: J19.6, J29.R7 (TD3-)
ETH1_3P: J19.8, J29.R6 (TD3+)
ETH1_4N: J19.4, J29.R8 (TD4+)
ETH1_4P: J19.2, J29.R9 (TD4-)
ETH_CT: C301.1, J29.R1 (CT), R301.1
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
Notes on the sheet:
Цепи соединены глобальными метками. Элементы J1–J16: нечётный ряд — усилитель MAX98357A, чётный — микрофон ICS-43434. J20 = гребёнка P2, J21 = P3 платы расширения Colorlight i9 (шлейфы IDC 2x15, контакт в контакт).

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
